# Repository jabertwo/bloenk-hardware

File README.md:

Blönk USB Notifier
=========
Schematics, PCB Layout and Windows Drivers

About
--
Blönk is an universal RGB light attached to the USB port. Originally designt as notifier for the Microsoft Lync software, Blönk now can be used for many other applications.

Flexibility
--
You can ether integrate Blönk into your own projects by using the .NET Library (or commandline software) or you can use Blönk with the already build software as Microsoft Lync notifier.

Software
--
You can find the sourcecode for the .NET library and software (also Lync integration) in a separate repository: https://github.com/johannes85/bloenk-software  
I also published more details about the project on my YouTube channel and website (in German): 
http://www.domestichacks.info/projekte/bloenk-usb-licht-fuer-lync/  
https://www.youtube.com/domestichacks

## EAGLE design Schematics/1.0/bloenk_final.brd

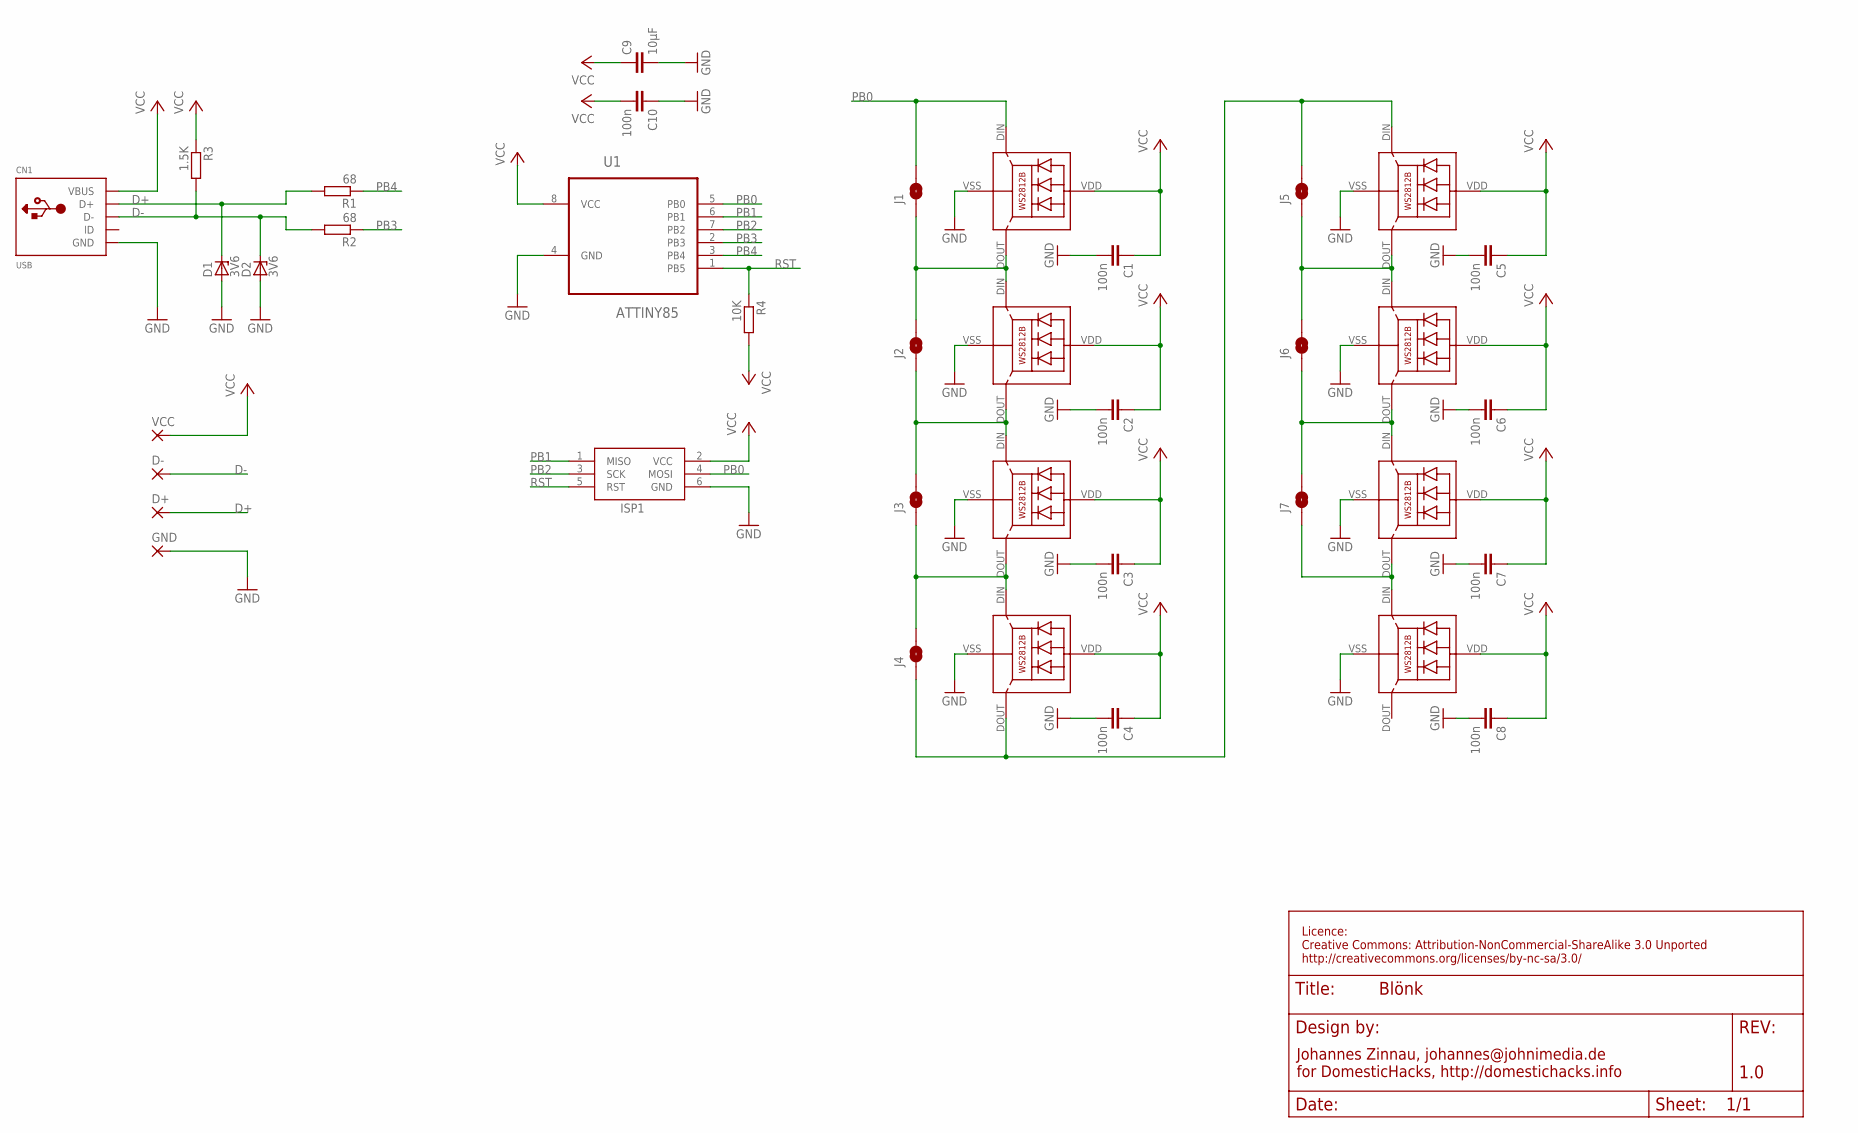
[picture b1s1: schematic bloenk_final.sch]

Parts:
C1, C2, C3, C4, C5, C6, C7, C8, C10: 100n; C0603
C9: 10µF; C0805
CN1: USB; USB-MINIB
D1, D2: 3V6; SOD80C
D+: SMD2; SMD1,27-2,54
D-: SMD2; SMD1,27-2,54
GND: SMD2; SMD1,27-2,54
ISP1: AVRISP-6; AVRISP
J1, J2, J3, J4, J5, J6, J7: SOLDERJUMPERNO; SJ_2S-NO
LED1, LED2, LED3, LED4, LED5, LED6, LED7, LED8: WS2812B
R1, R2: 68; R0603
R3: 1.5K; R0603
R4: 10K; R0603
U1: ATTINY85; SOIC127P798X216-8N
VCC: SMD2; SMD1,27-2,54

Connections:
D+: CN1.D+, D1.C, D+.1, R1.2
D-: CN1.D-, D2.C, D-.1, R2.2, R3.2
GND: C1.2, C2.2, C3.2, C4.2, C5.2, C6.2, C7.2, C8.2, C9.2, C10.1, CN1.GND, D1.A, D2.A, GND.1, ISP1.6 (GND), LED1.VSS (GND), LED2.VSS (GND), LED3.VSS (GND), LED4.VSS (GND), LED5.VSS (GND), LED6.VSS (GND), LED7.VSS (GND), LED8.VSS (GND), U1.4 (GND)
unnamed: J2.1, J3.2, LED2.DOUT (DO), LED3.DIN (DI)
unnamed: J3.1, J4.2, LED3.DOUT (DO), LED4.DIN (DI)
unnamed: J1.1, J2.2, LED1.DOUT (DO), LED2.DIN (DI)
unnamed: J5.1, J6.2, LED5.DOUT (DO), LED6.DIN (DI)
unnamed: J6.1, J7.2, LED6.DOUT (DO), LED7.DIN (DI)
unnamed: J7.1, LED7.DOUT (DO), LED8.DIN (DI)
unnamed: J4.1, J5.2, LED4.DOUT (DO), LED5.DIN (DI)
PB0: ISP1.4 (MOSI), J1.2, LED1.DIN (DI), U1.5 (PB0)
PB1: ISP1.1 (MISO), U1.6 (PB1)
PB2: ISP1.3 (SCK), U1.7 (PB2)
PB3: R2.1, U1.2 (PB3)
PB4: R1.1, U1.3 (PB4)
RST: ISP1.5 (RST), R4.1, U1.1 (PB5)
VCC: C1.1, C2.1, C3.1, C4.1, C5.1, C6.1, C7.1, C8.1, C9.1, C10.2, CN1.VBUS, ISP1.2 (VCC), LED1.VDD, LED2.VDD, LED3.VDD, LED4.VDD, LED5.VDD, LED6.VDD, LED7.VDD, LED8.VDD, R3.1, R4.2, U1.8 (VCC), VCC.1

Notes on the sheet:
Johannes Zinnau, johannes@johnimedia.de for DomesticHacks, http://domestichacks.info
1.0
Licence: Creative Commons: Attribution-NonCommercial-ShareAlike 3.0 Unported http://creativecommons.org/licenses/by-nc-sa/3.0/

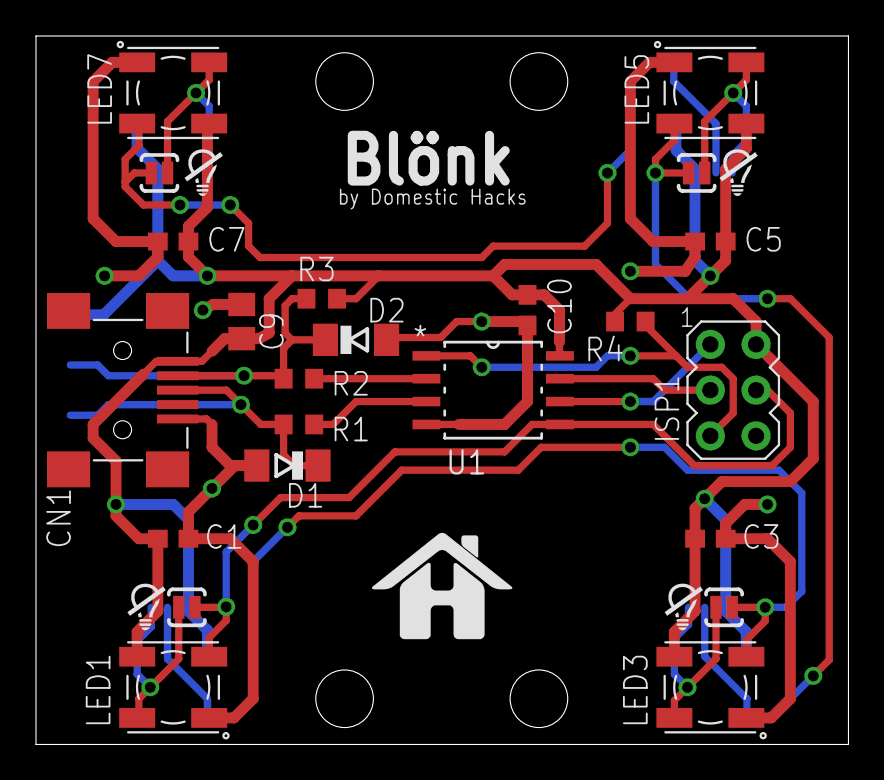
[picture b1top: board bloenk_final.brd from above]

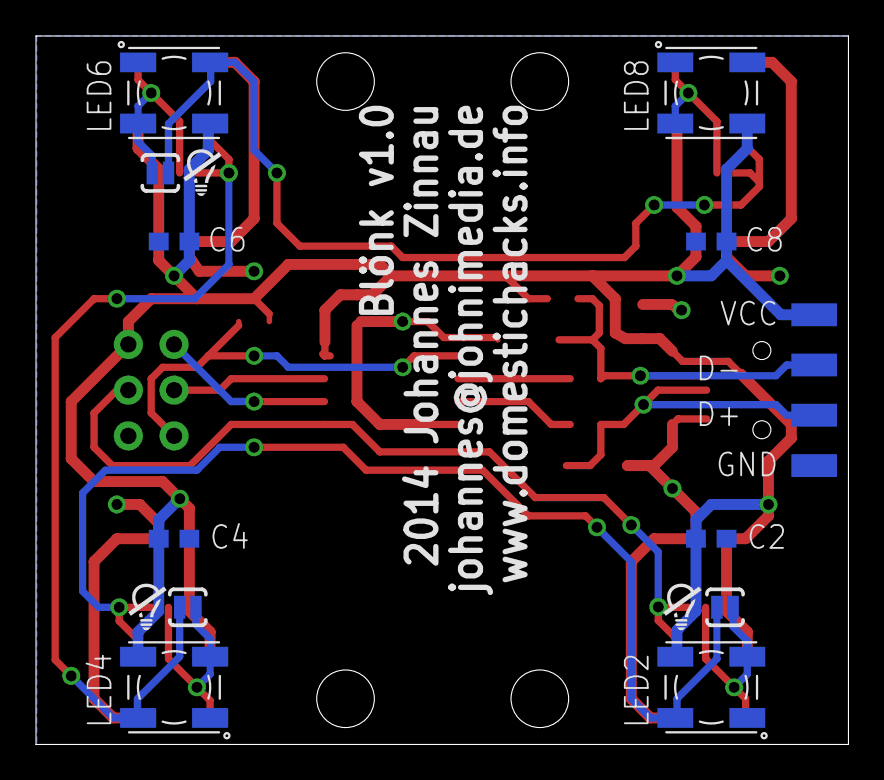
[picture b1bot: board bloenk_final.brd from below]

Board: 2 copper layers, 45.1 x 39.4 mm, 46 parts (18 on the bottom side), 17 nets.

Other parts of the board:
U$1, U$2, U$3, U$4, U$5, U$6, U$7: BULB
U$9: DH

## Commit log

2014-06-24 Initial release
2014-06-24 Moved license file for the hardware Added readme
2025-03-05 WIP new kicad version of pcb with usb type c

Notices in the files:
parts and their libraries:
SparkFun-Passives: Licensing: CC v3.0 Share-Alike You are welcome to use this library for commercial purposes.
